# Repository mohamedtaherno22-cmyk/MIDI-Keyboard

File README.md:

# MIDI Keypad

This is my attempt at designing my own MIDI keypad from scratch. I took inspiration from devices like the AKAI MPK Mini MK3, KORG nanoKEY2 and the keypad created by the Hack Club team. I used KiCad for the schematic and PCB design, with an ESP32S as the MCU.

Features
- 9 capacitive touch keys
- 3 rotary encoders
- 4 mechanical keyboard switches
- 2 slide potentiometers
- ESP32S-30pins

A large PCB with dimensions of (140 mm × 90 mm)

A smaller version designed to fit within a 100 × 100 mm board

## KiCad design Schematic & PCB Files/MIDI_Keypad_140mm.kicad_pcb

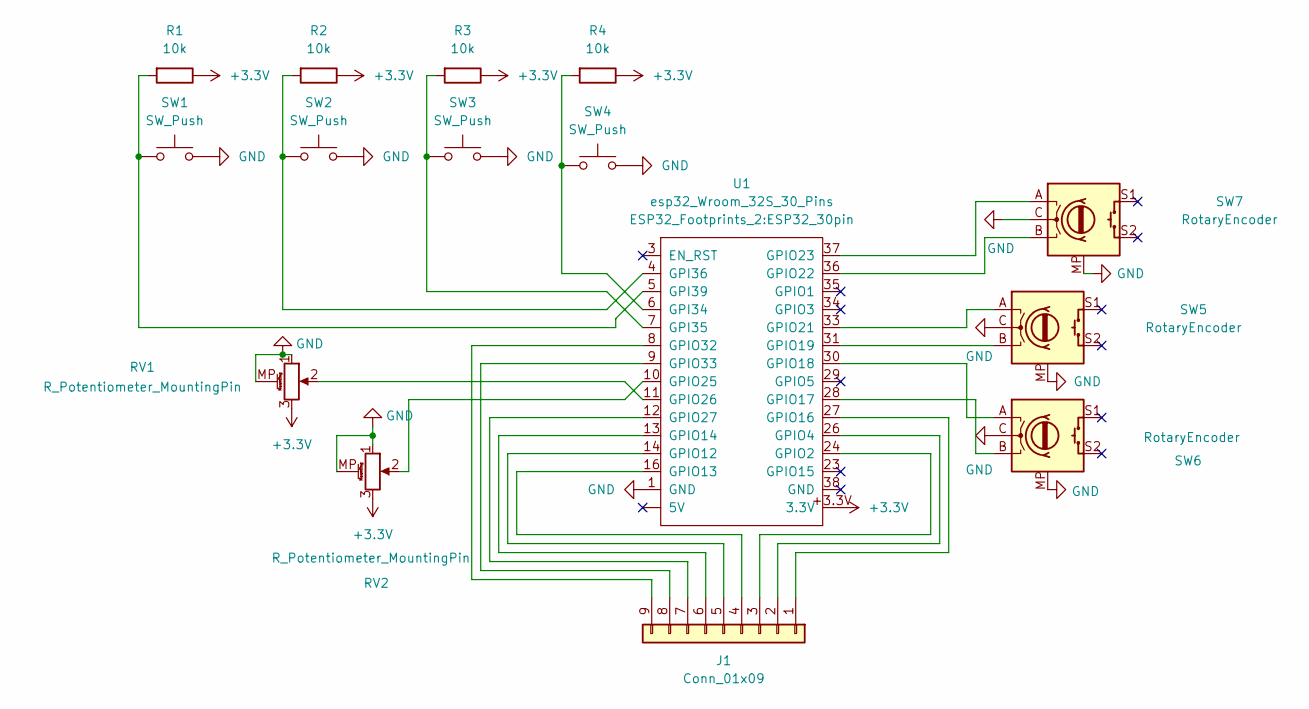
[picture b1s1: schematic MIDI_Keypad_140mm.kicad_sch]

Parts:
J1: Conn_01x09; Touch Keys
R1, R2, R3, R4: 10k; R_Axial_DIN0207_L6.3mm_D2.5mm_P10.16mm_Horizontal
RV1, RV2: R_Potentiometer_MountingPin; Potentiometer_Bourns_PTA2043_Single_Slide
SW1, SW2, SW3, SW4: SW_Push; SW_Cherry_MX_1.00u_PCB
SW5, SW6, SW7: RotaryEncoder; RotaryEncoder_Alps_EC11E-Switch_Vertical_H20mm
U1: esp32_Wroom_32S_30_Pins; ESP32_30pin

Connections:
+3.3V: R1.1, R2.1, R3.1, R4.1, RV1.3, RV2.3, U1.+3.3V (3.3V)
GND: RV1.1, RV1.MP (MountPin), RV2.1, RV2.MP (MountPin), SW1.2, SW2.2, SW3.2, SW4.2, SW5.C, SW5.MP, SW6.C, SW6.MP, SW7.C, SW7.MP, U1.1 (GND)
unnamed: J1.1, U1.27 (GPIO16)
unnamed: J1.2, U1.26 (GPIO4)
unnamed: J1.3, U1.24 (GPIO2)
unnamed: J1.4, U1.16 (GPIO13)
unnamed: J1.5, U1.14 (GPIO12)
unnamed: J1.6, U1.13 (GPIO14)
unnamed: J1.7, U1.12 (GPIO27)
unnamed: J1.8, U1.9 (GPIO33)
unnamed: J1.9, U1.8 (GPIO32)
unnamed: R4.2, SW4.1, U1.6 (GPI34)
unnamed: R3.2, SW3.1, U1.7 (GPI35)
unnamed: R2.2, SW2.1, U1.4 (GPI36)
unnamed: R1.2, SW1.1, U1.5 (GPI39)
unnamed: SW6.B, U1.28 (GPIO17)
unnamed: SW6.A, U1.30 (GPIO18)
unnamed: SW5.B, U1.31 (GPIO19)
unnamed: SW5.A, U1.33 (GPIO21)
unnamed: SW7.B, U1.36 (GPIO22)
unnamed: SW7.A, U1.37 (GPIO23)
unnamed: RV2.2, U1.10 (GPIO25)
unnamed: RV1.2, U1.11 (GPIO26)

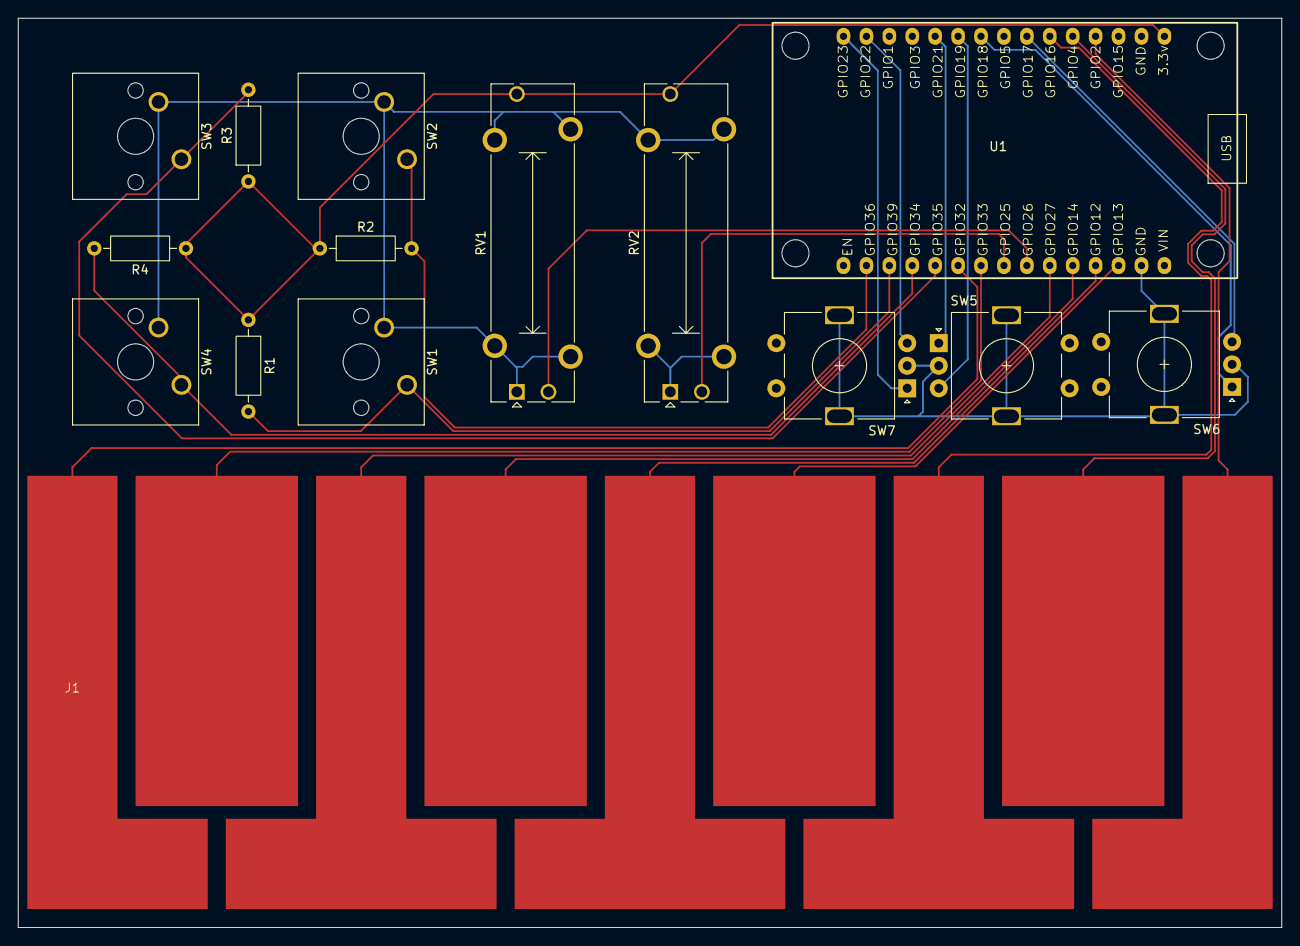
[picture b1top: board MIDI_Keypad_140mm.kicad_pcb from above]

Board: 2 copper layers, 140.0 x 100.8 mm, 15 parts (0 on the bottom side), 23 nets.
